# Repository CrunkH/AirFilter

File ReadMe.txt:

This will be the repository for all code related to the air filter project.

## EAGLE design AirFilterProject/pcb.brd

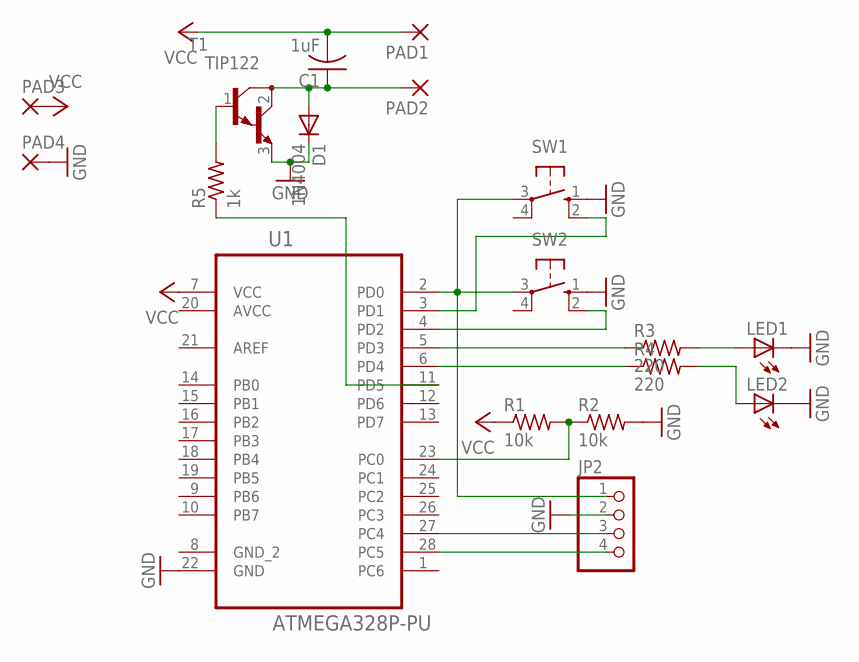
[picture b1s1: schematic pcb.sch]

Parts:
C1: 1uF; C025-025X050
D1: 1N4004; DO41-10
JP2: PINHD-1X4; 1X04
LED1, LED2: LED5MM
PAD1, PAD2, PAD3, PAD4: 1,6/0,8
R1, R2: 10k; 0204/5
R3, R4: 220; 0204/5
R5: 1k; 0204/5
SW1, SW2: 10-XX; B3F-10XX
T1: TIP122; TO220
U1: ATMEGA328P-PU; DIP254P762X457-28

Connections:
AVCC: U1.20 (AVCC)
GND: D1.C, JP2.2, LED1.K (C), LED2.K (C), PAD4.1, R2.2, SW1.1 (S), SW2.1 (S), T1.3 (E), U1.22 (GND)
unnamed: JP2.3, U1.27 (PC4)
unnamed: C1.1, D1.A, PAD2.1, T1.2 (C)
unnamed: JP2.4, U1.28 (PC5)
unnamed: R1.2, R2.1, U1.23 (PC0)
unnamed: JP2.1, SW1.3, SW2.3, U1.2 (PD0)
unnamed: SW1.2 (S1), U1.3 (PD1)
unnamed: SW2.2 (S1), U1.4 (PD2)
unnamed: R3.1, U1.5 (PD3)
unnamed: R4.1, U1.6 (PD4)
unnamed: LED1.A, R3.2
unnamed: LED2.A, R4.2
unnamed: R5.2, T1.1 (B)
unnamed: R5.1, U1.11 (PD5)
VCC: C1.2, PAD1.1, PAD3.1, R1.1, U1.7 (VCC)

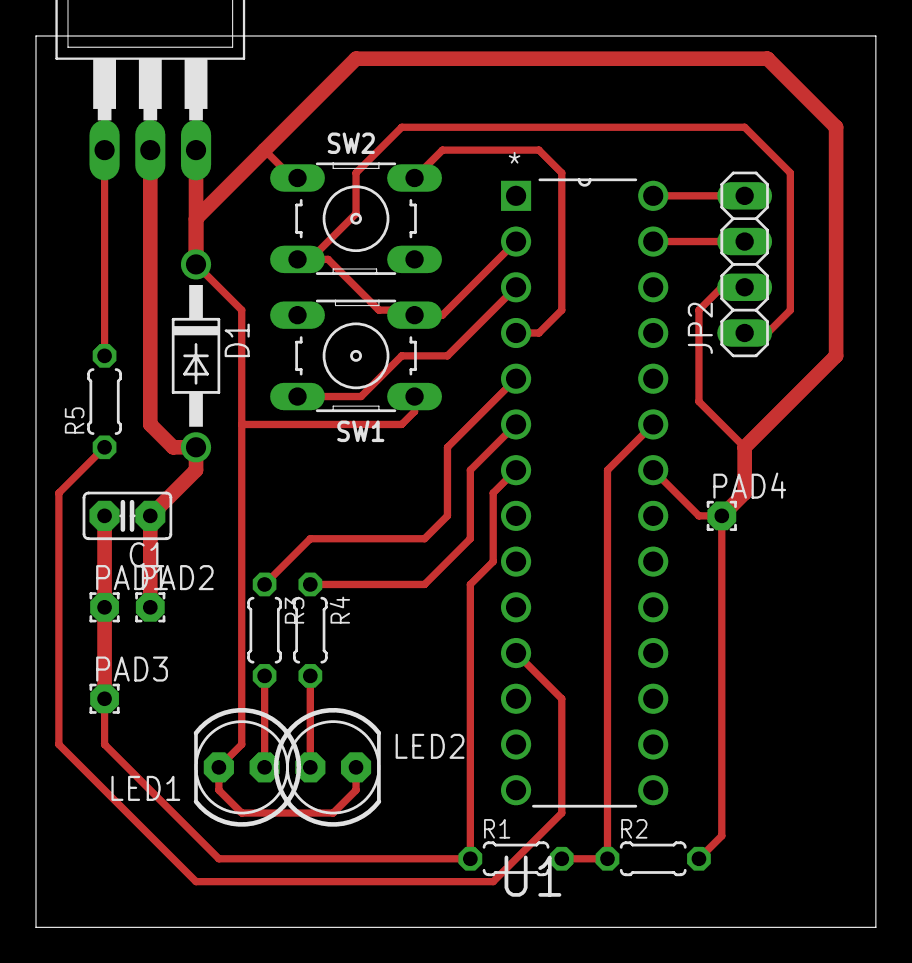
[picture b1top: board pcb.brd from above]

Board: 2 copper layers, 46.7 x 49.5 mm, 18 parts (0 on the bottom side), 15 nets.

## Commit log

2016-10-31 :neckbeard: Added .gitattributes & .gitignore files
2016-10-31 Update to Reps
    Updating Reps
2016-10-31 Eagle Updates
    Updates to Eagle Files
2016-10-31 Updates to Eagle
    Updates
2016-11-01 Final PCB
    Final Changes to PCB. Ready for printing
2016-11-01 Cleanup
    Cleanup
